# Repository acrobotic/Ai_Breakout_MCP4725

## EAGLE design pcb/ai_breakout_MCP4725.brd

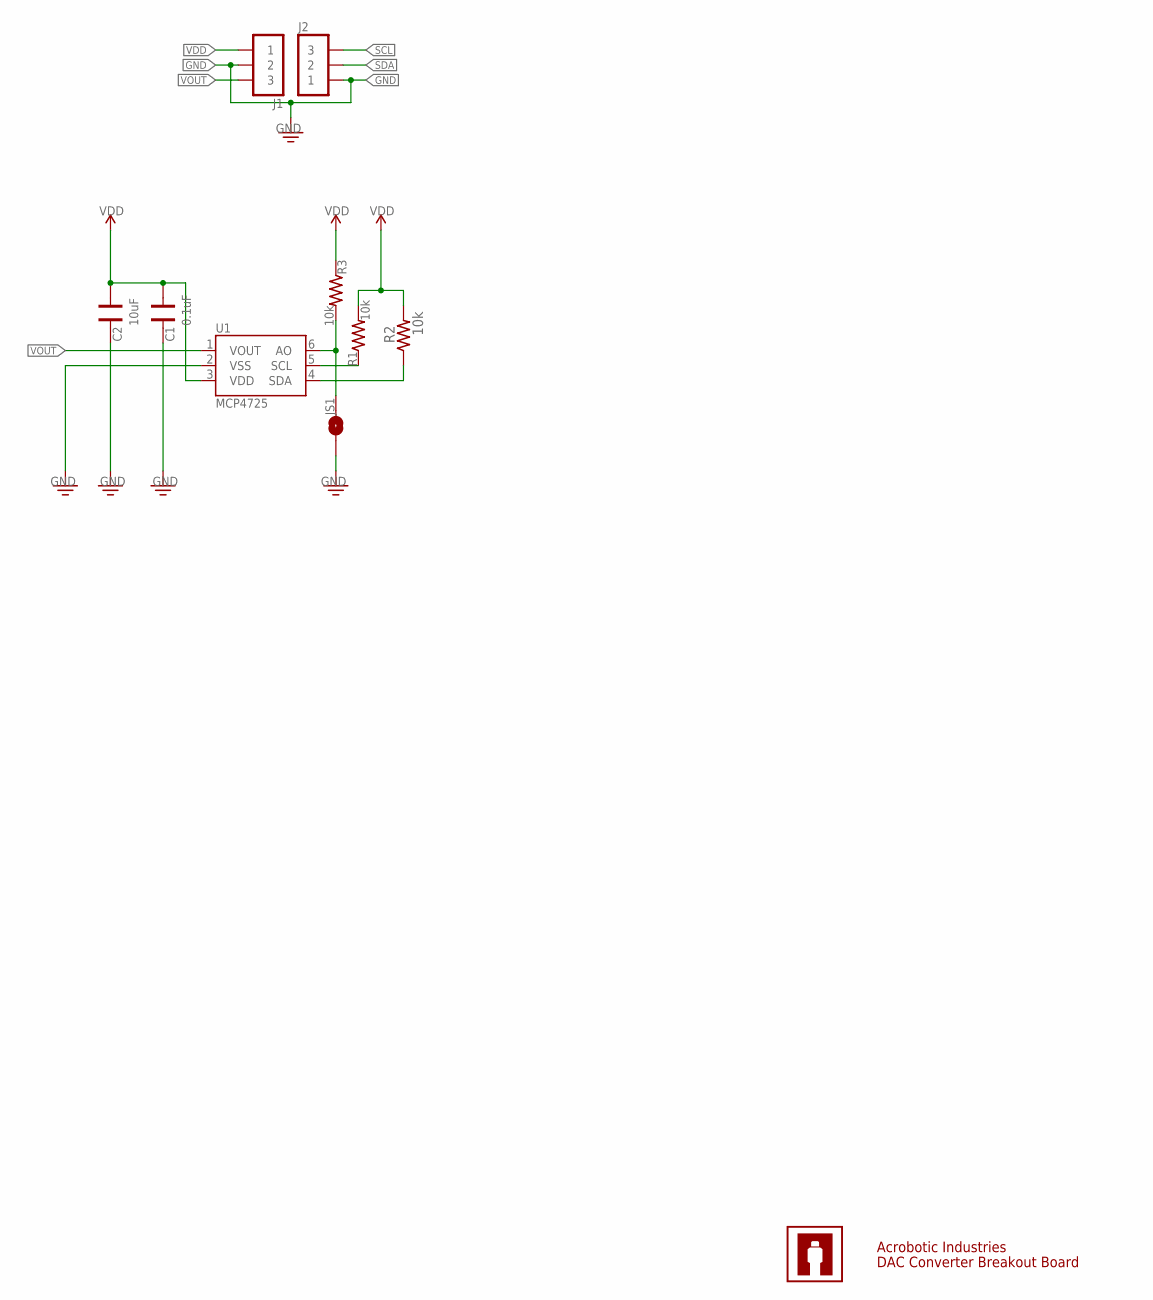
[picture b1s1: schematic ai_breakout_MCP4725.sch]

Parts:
C1: 0.1uF; CAP-0603
C2: 10uF; CAP-0603
J1: 1X03
J2: 1X03NOFIRST; 1X03-NOFIRST
JS1: 1X02-SJ-NO
R1, R2, R3: 10k; RES-0603
U1: MCP4725SOT-23; SOT23-6
U$4: AI-LOGOXS; AI-LOGO-XS

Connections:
GND: C1.2, C2.2, J1.2, J2.1, JS1.1, U1.2 (VSS)
SCL: J2.3, R1.1, U1.5 (SCL)
SDA: J2.2, R2.1, U1.4 (SDA)
VDD: C1.1, C2.1, J1.1, JS1.2, R1.2, R2.2, R3.1, R3.2, U1.3 (VDD), U1.6 (AO)
VOUT: J1.3, U1.1 (VOUT)

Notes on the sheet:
Acrobotic Industries
DAC Converter Breakout Board

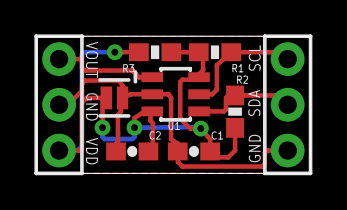
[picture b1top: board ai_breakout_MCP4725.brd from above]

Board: 2 copper layers, 15.2 x 7.6 mm, 10 parts (1 on the bottom side), 5 nets.

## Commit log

2015-05-28 deleted unnecessary files
2015-06-02 gerber file created
